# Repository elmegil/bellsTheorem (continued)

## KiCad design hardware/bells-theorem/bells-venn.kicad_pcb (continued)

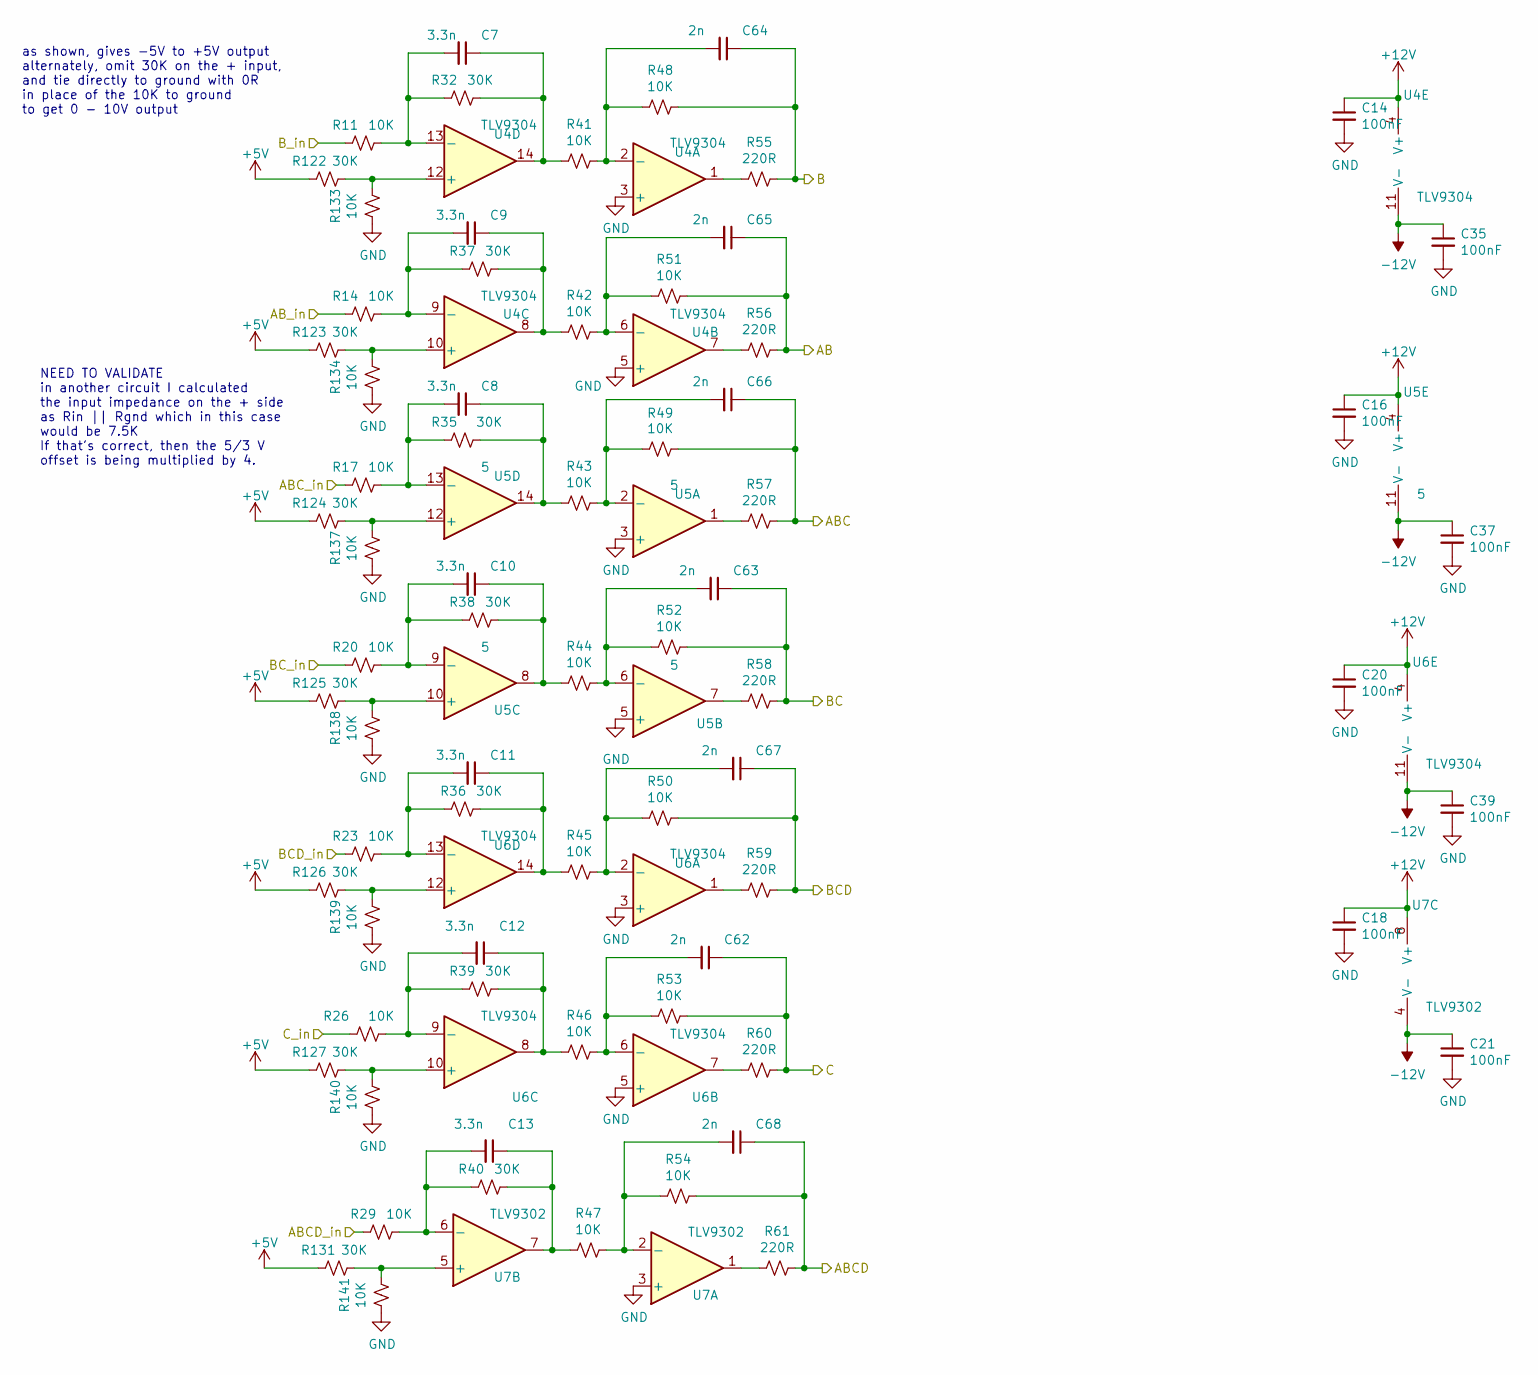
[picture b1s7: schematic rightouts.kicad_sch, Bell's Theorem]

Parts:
C7, C8, C9, C10, C11, C12, C13: 3.3n; C_0805_2012Metric_Pad1.18x1.45mm_HandSolder
C14, C16, C18, C20, C21, C35, C37, C39: 100nF; C_0805_2012Metric_Pad1.18x1.45mm_HandSolder
C62, C63, C64, C65, C66, C67, C68: 2n; C_0805_2012Metric_Pad1.18x1.45mm_HandSolder
R11, R14, R17, R20, R23, R26, R29, R41, R42, R43, R44, R45, R46, R47, R48, R49, R50, R51, R52, R53, R54, R133, R134, R137, R138, R139, R140, R141: 10K; R_0805_2012Metric_Pad1.20x1.40mm_HandSolder
R32, R35, R36, R37, R38, R39, R40, R122, R123, R124, R125, R126, R127, R131: 30K; R_0805_2012Metric_Pad1.20x1.40mm_HandSolder
R55, R56, R57, R58, R59, R60, R61: 220R; R_0805_2012Metric_Pad1.20x1.40mm_HandSolder
U4, U6: TLV9304; SOIC-14_3.9x8.7mm_P1.27mm
U5: 5; SOIC-14_3.9x8.7mm_P1.27mm
U7: TLV9302; SOIC-8_3.9x4.9mm_P1.27mm

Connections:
+5V: R122.2, R123.2, R124.2, R125.2, R126.2, R127.2, R131.2; also elsewhere on the board
+12V: C14.1, C16.1, C18.1, C20.1, U4.4 (V+), U5.4 (V+), U6.4 (V+), U7.8 (V+); also elsewhere on the board
-12V: C21.1, C35.1, C37.1, C39.1, U4.11 (V-), U5.11 (V-), U6.11 (V-), U7.4 (V-); also elsewhere on the board
/main/AB: C65.1, R51.1, R56.1; also elsewhere on the board
/main/ABC: C66.1, R49.1, R57.1; also elsewhere on the board
/main/ABCD: C68.1, R54.1, R61.1; also elsewhere on the board
/main/B: C64.1, R48.1, R55.1; also elsewhere on the board
/main/BC: C63.1, R52.1, R58.1; also elsewhere on the board
/main/BCD: C67.1, R50.1, R59.1; also elsewhere on the board
/main/C: C62.1, R53.1, R60.1; also elsewhere on the board
/main/right outs/ABCD_in: R29.2; also elsewhere on the board
/main/right outs/ABC_in: R17.2; also elsewhere on the board
/main/right outs/AB_in: R14.2; also elsewhere on the board
/main/right outs/BCD_in: R23.2; also elsewhere on the board
/main/right outs/BC_in: R20.2; also elsewhere on the board
/main/right outs/B_in: R11.2; also elsewhere on the board
/main/right outs/C_in: R26.2; also elsewhere on the board
GND: C14.2, C16.2, C18.2, C20.2, C21.2, C35.2, C37.2, C39.2, R133.2, R134.2, R137.2, R138.2, R139.2, R140.2, R141.2, U4.3 (+), U4.5 (+), U5.3 (+), U5.5 (+), U6.3 (+), U6.5 (+), U7.3 (+); also elsewhere on the board
unnamed: C7.1, R32.1, R41.2, U4.14
unnamed: C7.2, R11.1, R32.2, U4.13 (-)
unnamed: C8.1, R35.1, R43.2, U5.14
unnamed: C8.2, R17.1, R35.2, U5.13 (-)
unnamed: C9.1, R37.1, R42.2, U4.8
unnamed: C9.2, R14.1, R37.2, U4.9 (-)
unnamed: C10.1, R38.1, R44.2, U5.8
unnamed: C10.2, R20.1, R38.2, U5.9 (-)
unnamed: C11.1, R36.1, R45.2, U6.14
unnamed: C11.2, R23.1, R36.2, U6.13 (-)
unnamed: C12.1, R39.1, R46.2, U6.8
unnamed: C12.2, R26.1, R39.2, U6.9 (-)
unnamed: C13.1, R40.1, R47.2, U7.7
unnamed: C13.2, R29.1, R40.2, U7.6 (-)
unnamed: C62.2, R46.1, R53.2, U6.6 (-)
unnamed: C63.2, R44.1, R52.2, U5.6 (-)
unnamed: C64.2, R41.1, R48.2, U4.2 (-)
unnamed: C65.2, R42.1, R51.2, U4.6 (-)
unnamed: C66.2, R43.1, R49.2, U5.2 (-)
unnamed: C67.2, R45.1, R50.2, U6.2 (-)
unnamed: C68.2, R47.1, R54.2, U7.2 (-)
unnamed: R55.2, U4.1
unnamed: R56.2, U4.7
unnamed: R57.2, U5.1
unnamed: R58.2, U5.7
unnamed: R59.2, U6.1
unnamed: R60.2, U6.7
unnamed: R61.2, U7.1
unnamed: R122.1, R133.1, U4.12 (+)
unnamed: R123.1, R134.1, U4.10 (+)
unnamed: R124.1, R137.1, U5.12 (+)
unnamed: R125.1, R138.1, U5.10 (+)
unnamed: R126.1, R139.1, U6.12 (+)
unnamed: R127.1, R140.1, U6.10 (+)
unnamed: R131.1, R141.1, U7.5 (+)

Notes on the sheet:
NEED TO VALIDATE in another circuit I calculated the input impedance on the + side as Rin || Rgnd which in this case would be 7.5K If that's correct, then the 5/3 V offset is being multiplied by 4.
as shown, gives -5V to +5V output alternately, omit 30K on the + input, and tie directly to ground with 0R in place of the 10K to ground to get 0 - 10V output

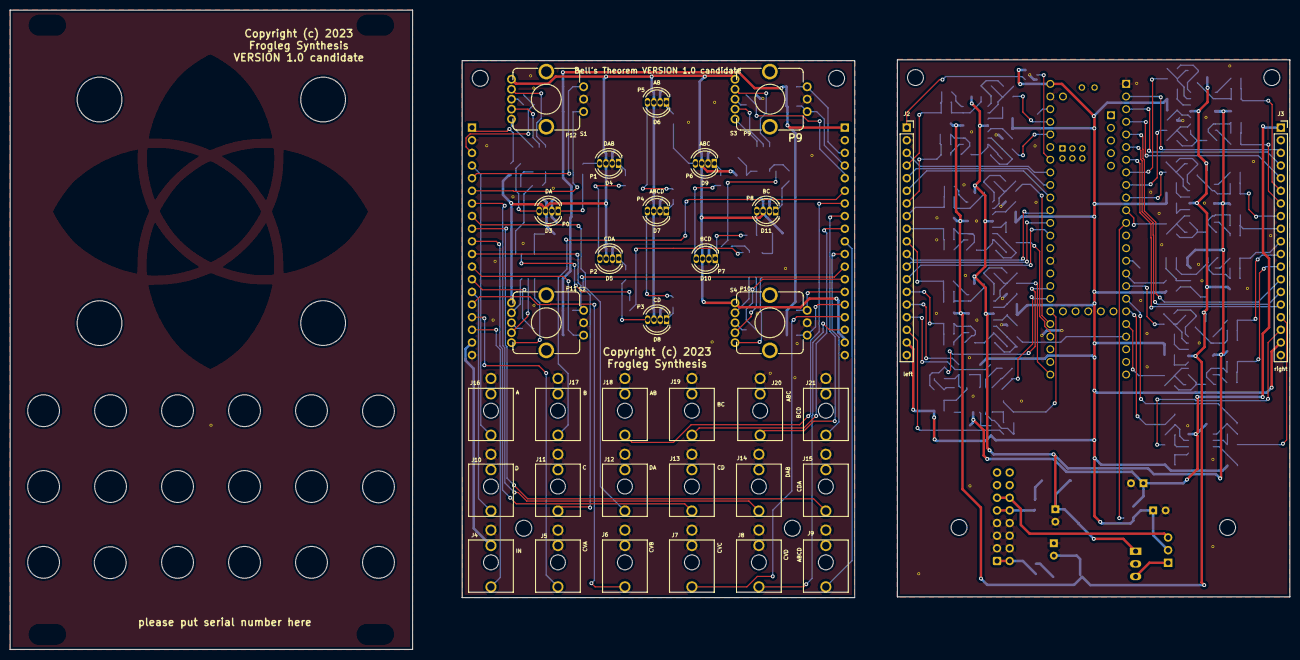
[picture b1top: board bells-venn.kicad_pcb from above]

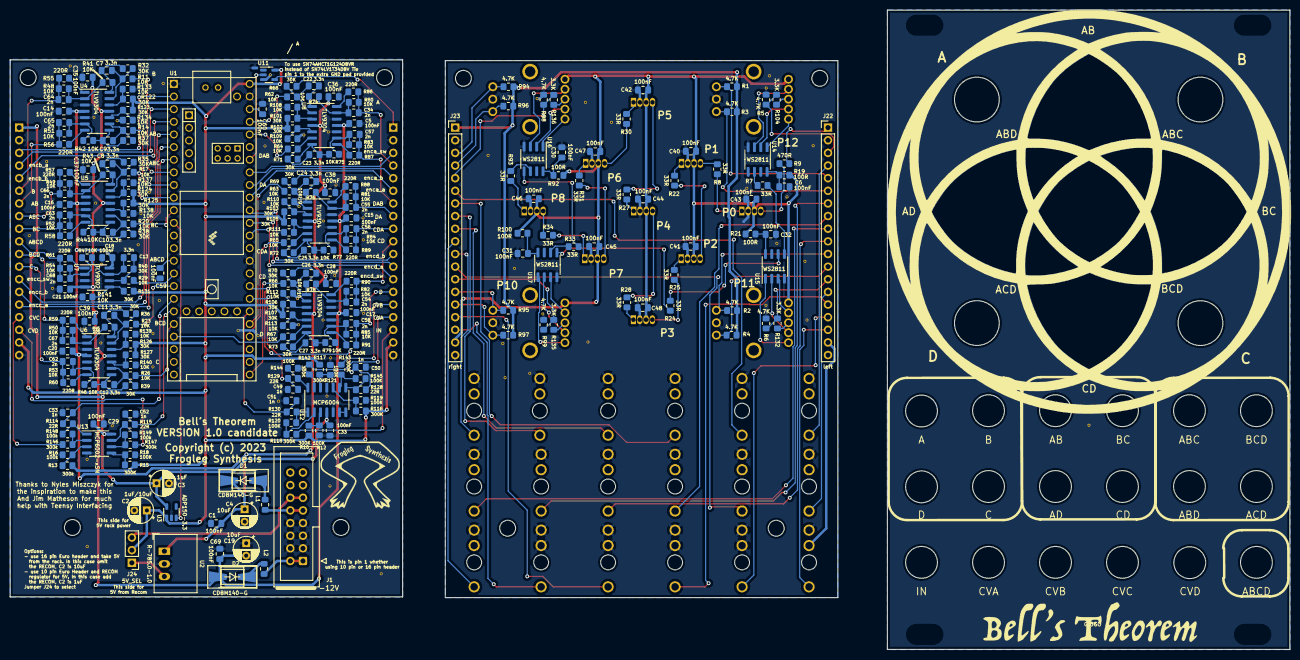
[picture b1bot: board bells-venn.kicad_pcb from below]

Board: 2 copper layers, 257.2 x 128.5 mm, 275 parts (242 on the bottom side), 190 nets.

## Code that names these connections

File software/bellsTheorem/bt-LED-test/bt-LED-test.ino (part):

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#define ENCDA 15
#define ENCDB 16
#define SWD 14
#define CVA A15
#define CVB A16
#define CVC A12
#define CVD A13
#define CV_IN A14
#define A 23
#define B 6
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#define BC 9
#define CD 33
#define DA 37
#define ABC 8
#define BCD 25
#define CDA 36
#define DAB 22
#define ABCD 24
#define NP 20
// there are 9, but in the prototype there's an extra one used for level shifting (???)
#define PC 13
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Bounce debD=Bounce();
Bounce *debounce[4] = {&debA, &debB, &debC, &debD} ; 

byte cv_in_pins[4] = { CVA, CVB, CVC, CVD };
long cv_values[4] = { 0, 0, 0, 0 };

byte resolution = 10;
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//
// ADC lib setup
//
byte inPins[5] = { CV_IN, CVA, CVB, CVC, CVD };
uint16_t inValues[5] = { 0, 0, 0, 0, 0 };
bool inFlags[5] = { false, false, false, false, false };

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
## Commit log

2020-10-23 Standard Teensy Encoder library (lots of jitter)
2020-10-24 Updated with Jim Matheson's encoder driver
2020-10-24 added debounced switch behavior (save current angle and reset to 0 degrees, press again and restore that previous angle)
2020-10-24 full basic functionality complete, but far from optimized
2020-10-24 update latest code and README
2020-10-29 add the kicad files
2021-03-29 take gerbers out of the repo, push latest updates
2021-03-30 revised LED drivers for encoders, fixed code in various places
2021-03-30 testing token
2021-05-05 version 0.3, update for corrected LED drivers, other tweaks
2021-10-01 updated for NeoPixels
2021-10-02 Update LICENSE
2021-10-06 last changes before major rework into JM's suggested MVC type architecture
2022-01-16 modified for Kicad 6 updated testing code
2022-01-16 updates to reflect KiCad 6 library changes revised level shifting for NeoPixels
2022-01-17 Modified with Jim M's recommendations for input scaling
2022-01-17 All changes up to date with latest revisions
2022-01-17 use new interrupt methods and do calculations core functionality complete
2022-01-17 experimenting with possible color schemes besides white
2022-09-14 last hardware / software updates
2022-11-29 committing changes including panel with proper keep-out
2022-11-29 deleting gerbers
2023-09-30 version 0.6 hardware and code
2023-11-29 current revision actually 0.6 was 1.0 candidate, but needs major revision
2026-04-26 checking in old outstanding changes prior to debugging with Claude Code
